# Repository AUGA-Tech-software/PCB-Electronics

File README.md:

# PCB-Electronics
 Projects of electronics projects on PCB

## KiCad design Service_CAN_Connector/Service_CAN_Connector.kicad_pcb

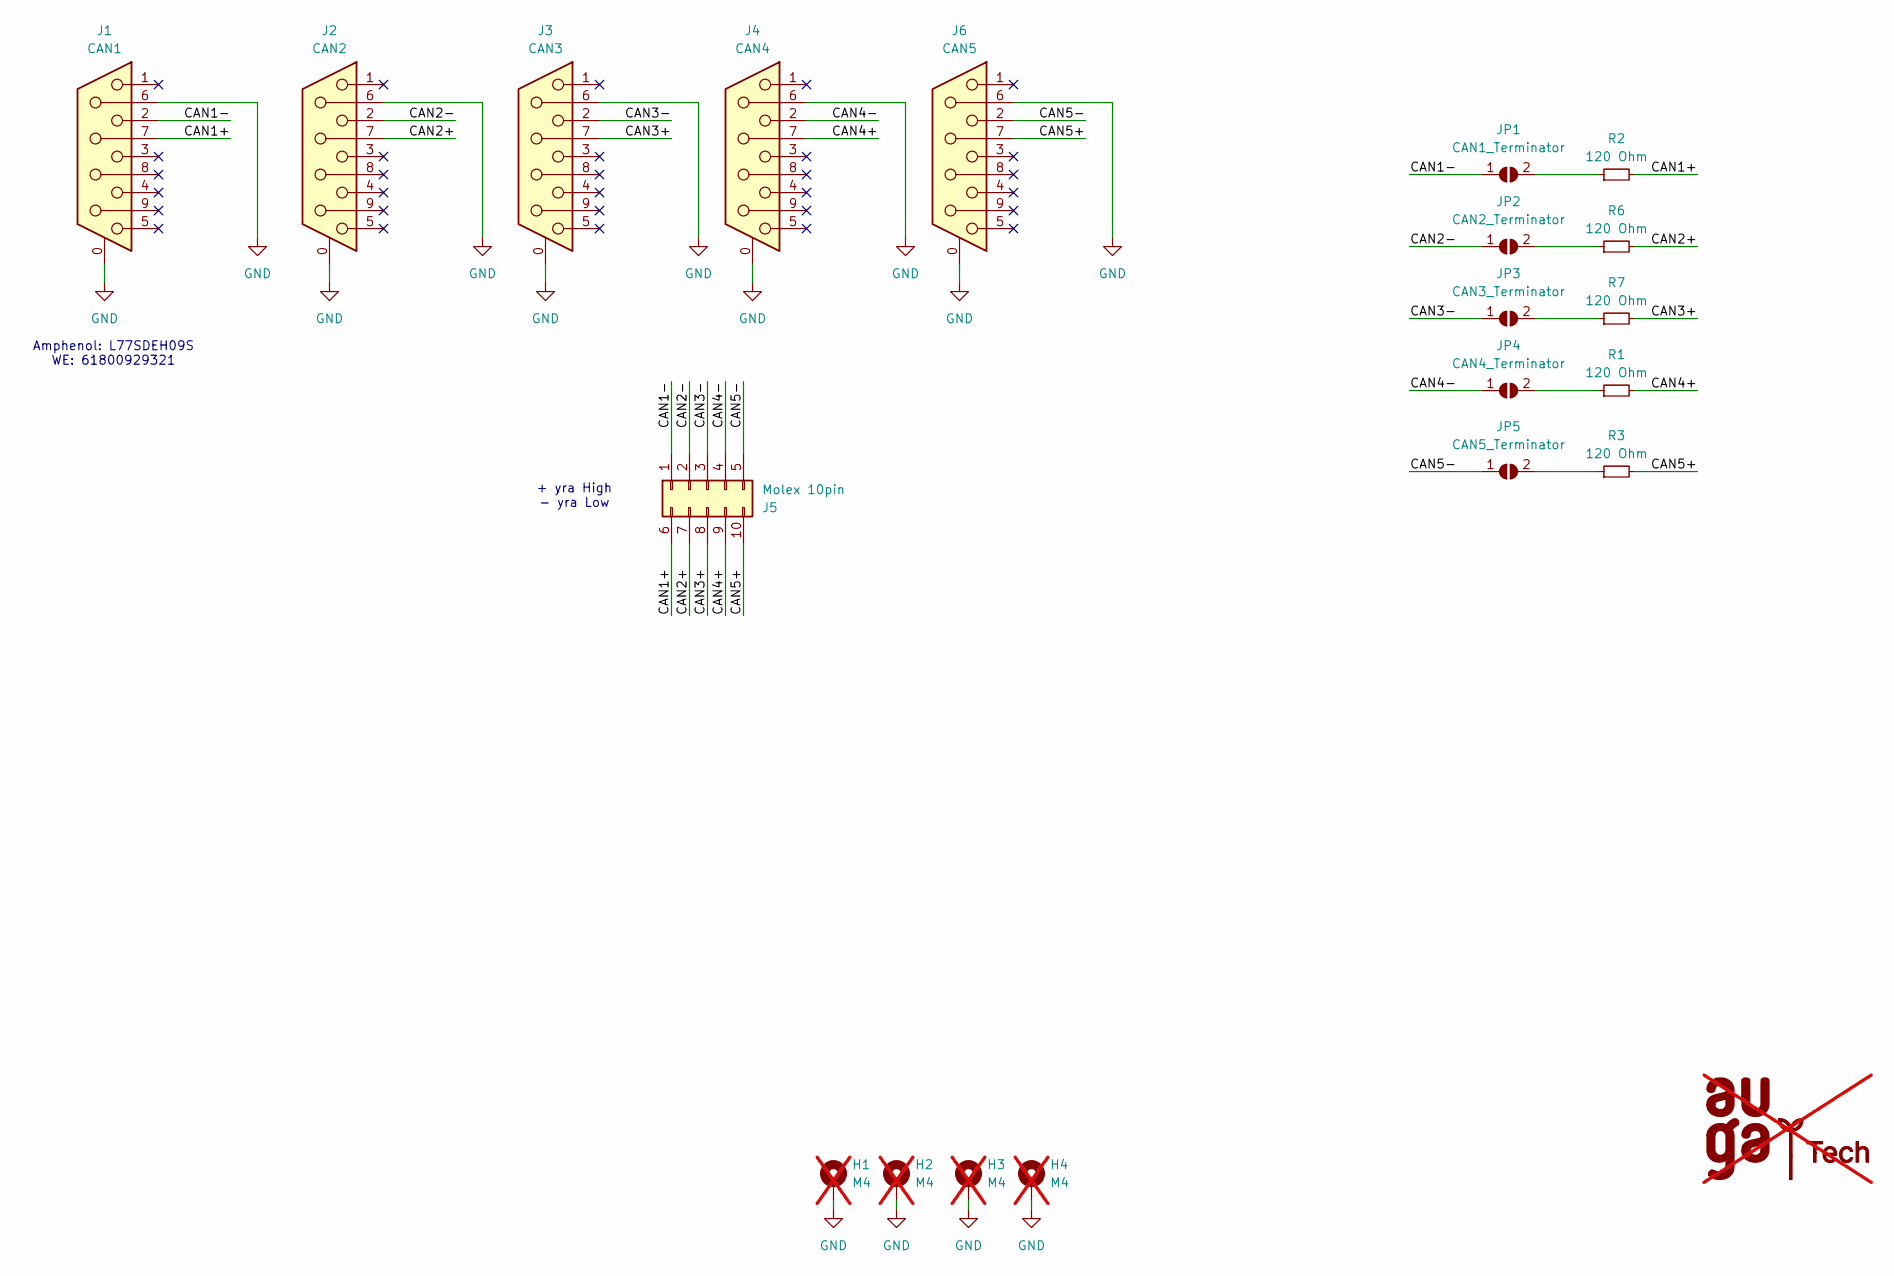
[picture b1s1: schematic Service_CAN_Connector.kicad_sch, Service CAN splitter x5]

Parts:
G1: AUGA-Tech-LOGO; AUGA-Tech-LOGO_12x15; not fitted
H1, H2, H3, H4: M4; MountingHole_4.3x6.2mm_M4_Pad_Via; not fitted
J1: CAN1; DSUB-9_Female_Vertical_P2.77x2.84mm_MountingHoles; JLCPCB Part # C19077342
J2: CAN2; DSUB-9_Female_Vertical_P2.77x2.84mm_MountingHoles; JLCPCB Part # C19077342
J3: CAN3; DSUB-9_Female_Vertical_P2.77x2.84mm_MountingHoles; JLCPCB Part # C19077342
J4: CAN4; DSUB-9_Female_Vertical_P2.77x2.84mm_MountingHoles; JLCPCB Part # C19077342
J5: Molex 10pin; Molex_Mini-Fit_Jr_5566-10A2_2x05_P4.20mm_Vertical; MFR_PN 39299103
J6: CAN5; DSUB-9_Female_Vertical_P2.77x2.84mm_MountingHoles; JLCPCB Part # C19077342
JP1: CAN1_Terminator; SolderJumper-2_P1.3mm_Open_RoundedPad1.0x1.5mm
JP2: CAN2_Terminator; SolderJumper-2_P1.3mm_Open_RoundedPad1.0x1.5mm
JP3: CAN3_Terminator; SolderJumper-2_P1.3mm_Open_RoundedPad1.0x1.5mm
JP4: CAN4_Terminator; SolderJumper-2_P1.3mm_Open_RoundedPad1.0x1.5mm
JP5: CAN5_Terminator; SolderJumper-2_P1.3mm_Open_RoundedPad1.0x1.5mm
R1, R2, R3, R6, R7: 120 Ohm; R_0805_2012Metric; JLCPCB Part # C17437

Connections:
/CAN1+: J1.7, J5.6, R2.2
/CAN1-: J1.2, J5.1, JP1.1 (A)
/CAN2+: J2.7, J5.7, R6.2
/CAN2-: J2.2, J5.2, JP2.1 (A)
/CAN3+: J3.7, J5.8, R7.2
/CAN3-: J3.2, J5.3, JP3.1 (A)
/CAN4+: J4.7, J5.9, R1.2
/CAN4-: J4.2, J5.4, JP4.1 (A)
/CAN5+: J5.10, J6.7, R3.2
/CAN5-: J5.5, J6.2, JP5.1 (A)
GND: H1.1, H2.1, H3.1, H4.1, J1.0 (PAD), J1.6, J2.0 (PAD), J2.6, J3.0 (PAD), J3.6, J4.0 (PAD), J4.6, J6.0 (PAD), J6.6
unnamed: JP1.2 (B), R2.1
unnamed: JP2.2 (B), R6.1
unnamed: JP3.2 (B), R7.1
unnamed: JP4.2 (B), R1.1
unnamed: JP5.2 (B), R3.1

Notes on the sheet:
Amphenol: L77SDEH09S WE: 61800929321
+ yra High - yra Low

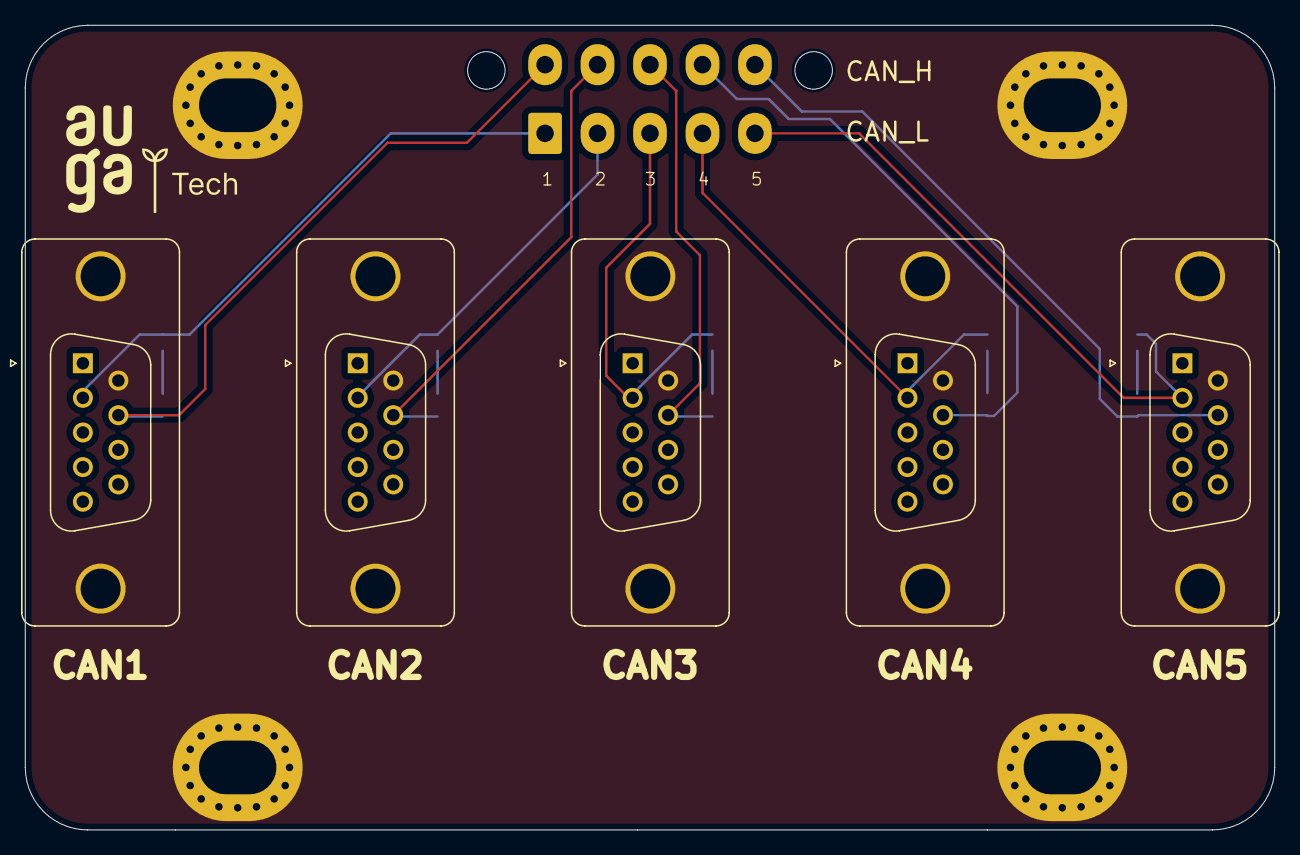
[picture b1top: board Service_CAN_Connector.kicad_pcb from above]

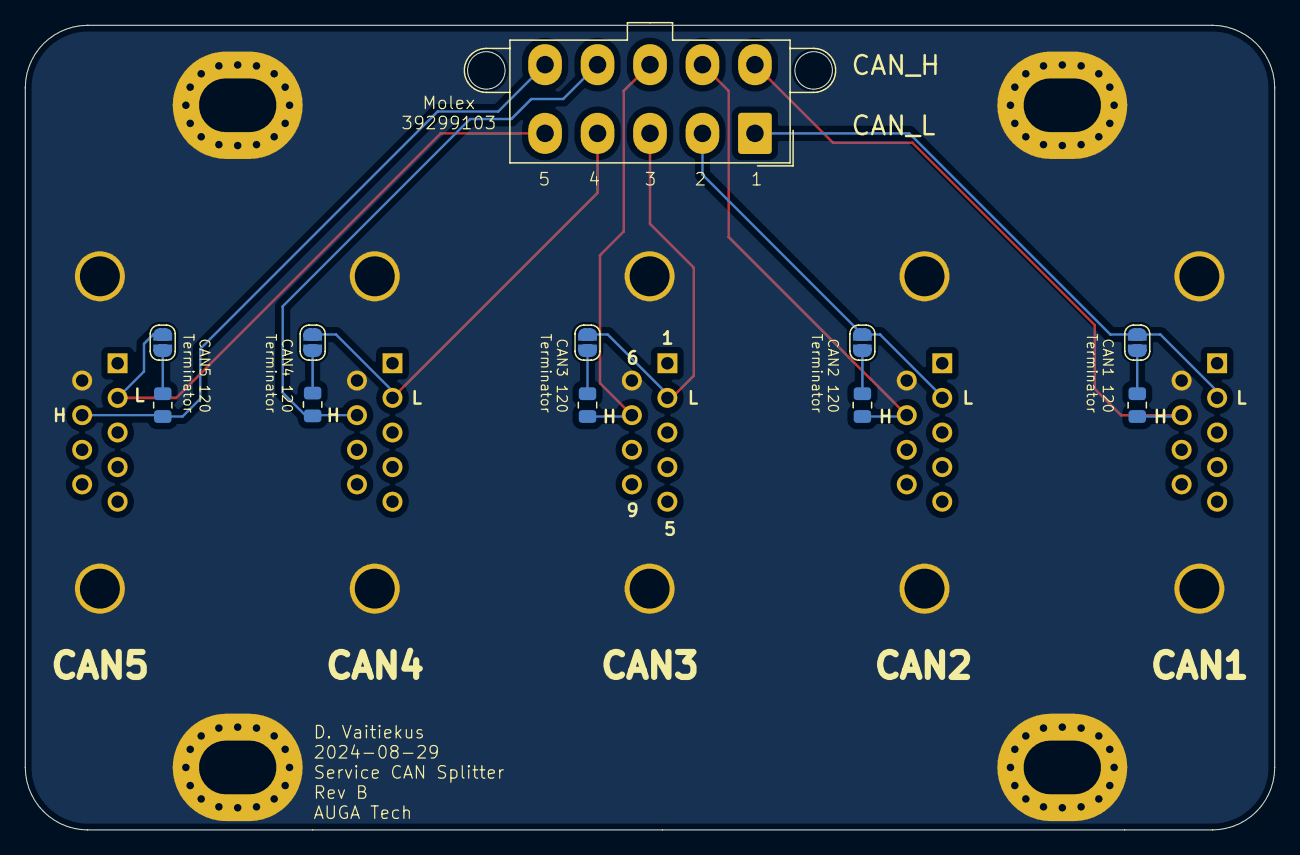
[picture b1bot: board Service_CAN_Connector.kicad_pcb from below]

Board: 2 copper layers, 100.0 x 64.4 mm, 21 parts (11 on the bottom side), 16 nets.

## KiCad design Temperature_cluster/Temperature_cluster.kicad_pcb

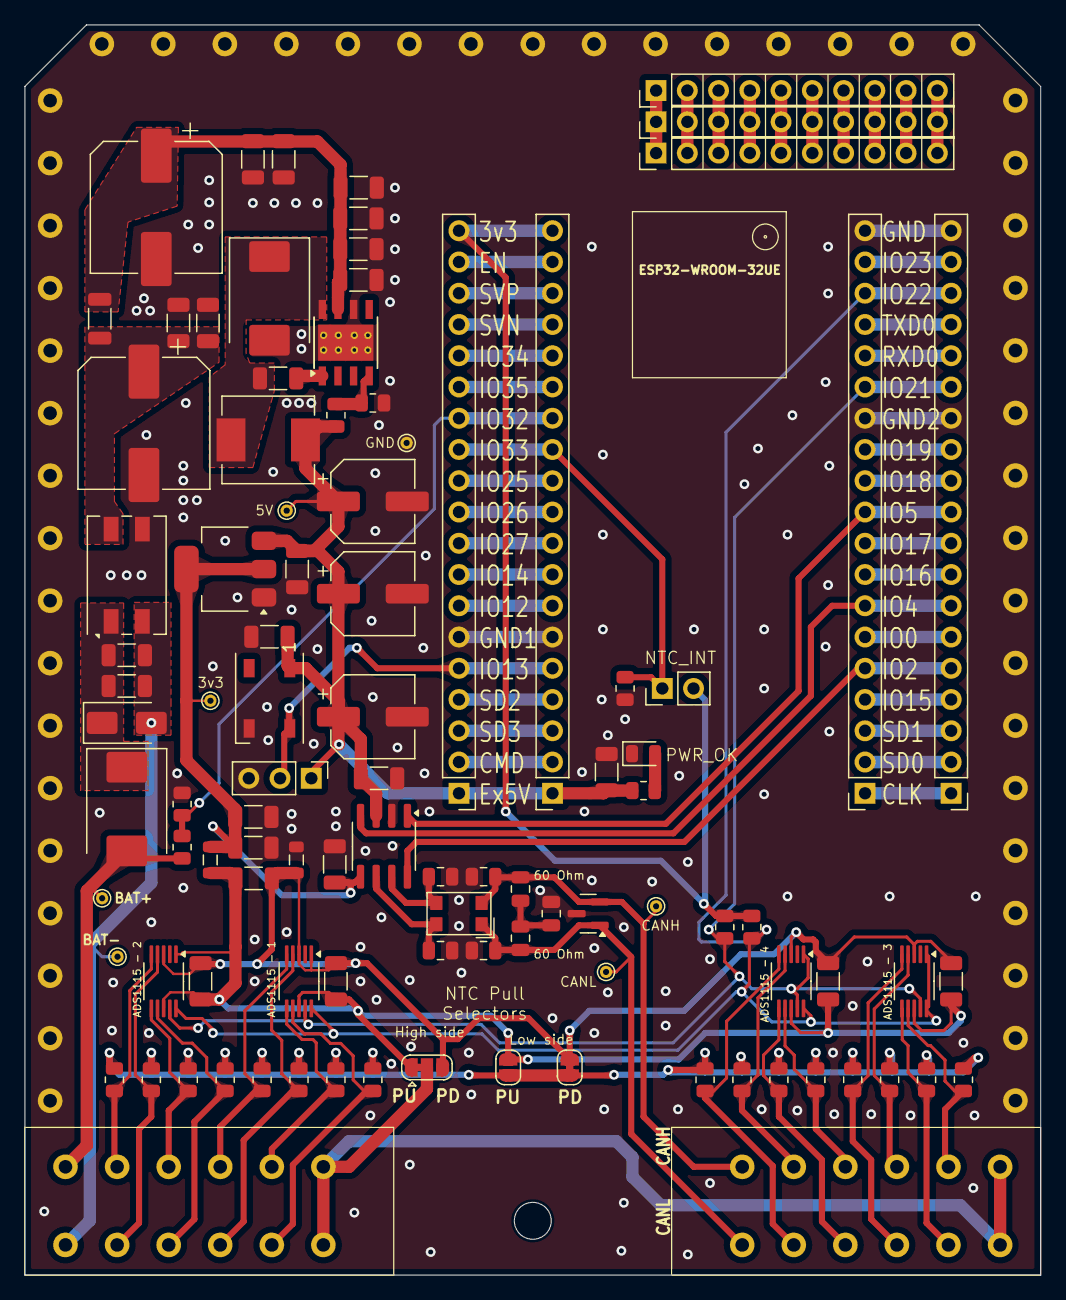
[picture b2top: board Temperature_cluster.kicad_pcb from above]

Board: 2 copper layers, 82.6 x 101.6 mm, 99 parts (1 on the bottom side), 81 nets.

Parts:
C1, C2, C7, C12, C16, C21, C22, C23, C25, C26, C28: 50V, 100nF; C_1206_3216Metric
C3, C4, C5, C6, C8, C9, C10, C11, C15, C20, C24: 50V, 10uF; C_1206_3216Metric
C13: 50V, 10nF; C_1206_3216Metric
C14, C19: 50v, 220uF; CP_Elec_10x10.5
C17, C18, C27: 10v, 220uF; CP_Elec_6.3x5.4
C29, C30, C31, C32: 100pF; C_0805_2012Metric
C33: 4n7 100V; C_0805_2012Metric
D1: WS2812B; LED_WS2812B_PLCC4_5.0x5.0mm_P3.2mm
D2, D4: B540C-13-F; D_SMC
D3: SMAJ26CA; D_SMA
D5: Power_OK; LED_0805_2012Metric
D6: NUP2105L; SOT-23
FB1, FB2: 500mA; L_0805_2012Metric
FL1: 500uH, 1kohm, 1A; Filter_Bourns_SRF0905_6.0x9.2mm
FL2: Filter_EMI; L_CommonModeChoke_1812
G1: AUGA-Tech-LOGO; AUGA-Tech-LOGO_23x15
J1: ESP32_Left; PinHeader_1x19_P2.54mm_Vertical
J2: DTM13-12PA-12PB; DTM13-12PA-12PB-R008
J3: ESP32_Right; PinHeader_1x19_P2.54mm_Vertical
J4: ESP32_Left; PinSocket_1x19_P2.54mm_Vertical
J5: ESP32_Right; PinSocket_1x19_P2.54mm_Vertical
J6: NTC_Internal; PinHeader_1x02_P2.54mm_Vertical
J7: EXTRA1; PinHeader_1x10_P2.54mm_Vertical
J8: EXTRA3; PinHeader_1x10_P2.54mm_Vertical
J9: EXTRA2; PinHeader_1x10_P2.54mm_Vertical
J10: Ext RGB connector; PinHeader_1x03_P2.54mm_Vertical
JP1: NTC-PullDown; SolderJumper-2_P1.3mm_Bridged_RoundedPad1.0x1.5mm
JP2: NTC-PullUp; SolderJumper-2_P1.3mm_Open_RoundedPad1.0x1.5mm
JP3: NTC_Input; SolderJumper-3_P1.3mm_Bridged12_RoundedPad1.0x1.5mm
L1: 15uH; L_Sunlord_MWSA0603S
L2: 2.2uH, 900mA; L_1206_3216Metric
R1, R2: 5.1k; R_0805_2012Metric
R7, R8, R9, R10, R11, R12, R13, R14, R15, R16, R17, R18, R19, R20, R21, R22, R24, R29, R30: 10K; R_0805_2012Metric
R23: 33k; R_0805_2012Metric
R25: 680; R_0805_2012Metric
R26, R27: 59R 1%; C_0805_2012Metric
R28: 100k; R_0805_2012Metric
TP1: VBat+; TestPoint_THTPad_D1.0mm_Drill0.5mm
TP2: VBat-; TestPoint_THTPad_D1.0mm_Drill0.5mm
TP3: 5V; TestPoint_THTPad_D1.0mm_Drill0.5mm
TP4: GND; TestPoint_THTPad_D1.0mm_Drill0.5mm
TP5: 3v3; TestPoint_THTPad_D1.0mm_Drill0.5mm
TP6: CANH; TestPoint_THTPad_D1.0mm_Drill0.5mm
TP7: CANL; TestPoint_THTPad_D1.0mm_Drill0.5mm
U2: ADS1115IDGS - 1; VSSOP-10_3x3mm_P0.5mm
U3: ADS1115IDGS - 3; VSSOP-10_3x3mm_P0.5mm
U4: ADS1115IDGS - 2; VSSOP-10_3x3mm_P0.5mm
U5: ADS1115IDGS - 4; VSSOP-10_3x3mm_P0.5mm
U6: TPS5430DDAR; TI_SO-PowerPAD-8_ThermalVias
U7: AMS1117-3.3; SOT-223-3_TabPin2
U8: TJA1051T-3; SOIC-8_3.9x4.9mm_P1.27mm

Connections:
+3.3VA: C3.2, C4.2, C5.2, C6.2, C25.1, FB1.2, JP2.2 (B), JP3.1 (A), U2.8 (VDD), U3.8 (VDD), U4.1 (ADDR), U4.8 (VDD), U5.8 (VDD)
+3.3VP: J3.19, J5.19, J6.2, R1.1, R2.1
+3V3: C23.2, C24.2, C26.1, FB1.1, TP5.1, U7.2 (VO), U8.5 (VIO)
+5V: C1.1, C2.1, C17.1, C18.1, C22.2, C27.1, C28.1, D1.1 (VDD), J3.1, J5.1, J10.1, L1.2, R23.2, R25.2, TP3.1, U7.3 (VI), U8.3 (VCC)
/CLK: J1.1, J4.1
/CMD: J3.2, J5.2
/EN: J3.18, J5.18
/IO0: J1.6, J4.6
/IO12: J3.7, J5.7
/IO14: J3.8, J5.8
/IO15: J1.4, J4.4
/IO16: J1.8, J4.8
/IO17: J1.9, J4.9
/IO18: J1.11, J4.11
/IO19: J1.12, J4.12
/IO23: J1.18, J4.18
/IO25: J3.11, J5.11
/IO26: J3.10, J5.10
/IO27: J3.9, J5.9
/IO34: J3.15, J5.15
/IO35: J3.14, J5.14
/NTC_1: J2.A8, R7.1, U4.5 (AIN1)
/NTC_2: J2.A9, R8.1, U4.6 (AIN2)
/NTC_3: J2.A10, R9.1, U2.5 (AIN1)
/NTC_4: J2.A11, R10.1, U2.6 (AIN2)
/NTC_5: J2.A2, R11.1, U2.7 (AIN3)
/NTC_6: J2.A3, R12.1, U2.4 (AIN0)
/NTC_7: J2.A4, R13.1, U4.7 (AIN3)
/NTC_8: J2.A5, R14.1, U4.4 (AIN0)
/NTC_9: J2.B2, R15.1, U5.4 (AIN0)
/NTC_10: J2.B3, R16.1, U5.7 (AIN3)
/NTC_11: J2.B4, R17.1, U3.4 (AIN0)
/NTC_12: J2.B5, R18.1, U3.7 (AIN3)
/NTC_13: J2.B8, R19.1, U3.6 (AIN2)
/NTC_14: J2.B9, R20.1, U3.5 (AIN1)
/NTC_15: J2.B10, R21.1, U5.6 (AIN2)
/NTC_16: J2.B11, R22.1, U5.5 (AIN1)
/NTC_INT: J3.12, J5.12, J6.1, R29.1
/NTC_Input: J2.A1, J2.A12, J2.B6, J2.B7, JP3.2 (C)
/Power_module/BOOT: C13.1, U6.1 (BOOT)
/Power_module/PH: C13.2, D4.1 (K), L1.1, U6.8 (PH)
/Power_module/VSENSE: R23.1, R24.2, U6.4 (VSENSE)
/RXD0: J1.15, J4.15
/SD0: J1.2, J4.2
/SD1: J1.3, J4.3
/SD2: J3.4, J5.4
/SD3: J3.3, J5.3
/TXD0: J1.16, J4.16
/VBAT_Sense: J3.13, J5.13, R28.2, R30.2
/VN: J3.16, J5.16
/VP: J3.17, J5.17
/WS_LED: D1.4 (DIN), J3.5, J5.5, J10.2
/i2c_ADDR-3: J1.17, J4.17, R2.2, U2.10 (SCL), U3.1 (ADDR), U3.10 (SCL), U4.10 (SCL), U5.10 (SCL)
/i2c_ADDR-4: J1.14, J4.14, R1.2, U2.9 (SDA), U3.9 (SDA), U4.9 (SDA), U5.1 (ADDR), U5.9 (SDA)
CAN_H: C31.2, D6.2 (K), FL2.2, J2.B1, R26.1, TP6.1
CAN_L: C32.1, D6.1 (K), FL2.1, J2.B12, R27.2, TP7.1
CAN_RX: J1.7, J4.7, U8.4 (RXD)
CAN_S: J1.5, J4.5, U8.8 (S)
CAN_TX: J1.10, J4.10, U8.1 (TXD)
GND: C1.2, C2.2, C7.2, C8.1, C9.1, C10.1, C14.2, C15.1, C16.2, C17.2, C18.2, C19.2, C20.1, C21.2, C22.1, C23.1, C24.1, C26.2, C27.2, C28.2, C29.2, C30.1, C31.1, C32.2, C33.2, D1.3 (VSS), D4.2 (A), D5.1 (K), D6.3 (A), FB2.1, FL1.3, J1.13, J1.19, J2.13 (GND), J3.6, J4.13, J4.19, J5.6, J10.3, R24.1, R29.2, R30.1, TP4.1, U6.6 (GND), U6.9 (GNDPAD), U7.1 (GND), U8.2 (GND)
GNDA: C3.1, C4.1, C5.1, C6.1, C25.2, FB2.2, JP1.2 (B), JP3.3 (B), U2.1 (ADDR), U2.3 (GND), U3.3 (GND), U4.3 (GND), U5.3 (GND)
unnamed: C14.1, C15.2, C16.1, FL1.4, L2.1
unnamed: C33.1, R26.2, R27.1
unnamed: C11.2, C12.1, D2.1 (K), D3.1 (A1), FL1.1
unnamed: D5.2 (A), R25.1
unnamed: J7.1, J8.1, J9.1
unnamed: J7.2, J8.2, J9.2
unnamed: J7.3, J8.3, J9.3
unnamed: J7.4, J8.4, J9.4
unnamed: J7.5, J8.5, J9.5
unnamed: J7.6, J8.6, J9.6
unnamed: J7.7, J8.7, J9.7
unnamed: J7.8, J8.8, J9.8
unnamed: J7.9, J8.9, J9.9
unnamed: J7.10, J8.10, J9.10
unnamed: JP1.1 (A), JP2.1 (A), R7.2, R8.2, R9.2, R10.2, R11.2, R12.2, R13.2, R14.2, R15.2, R16.2, R17.2, R18.2, R19.2, R20.2, R21.2, R22.2
unnamed: C30.2, FL2.3, U8.7 (CANH)
unnamed: C29.1, FL2.4, U8.6 (CANL)
VBat+: D2.2 (A), J2.A7, R28.1, TP1.1
VBat-: C11.1, C12.2, D3.2 (A2), FL1.2, J2.A6, TP2.1
Vin_Filtered: C7.1, C8.2, C9.2, C10.2, C19.1, C20.2, C21.1, L2.2, U6.7 (VIN)

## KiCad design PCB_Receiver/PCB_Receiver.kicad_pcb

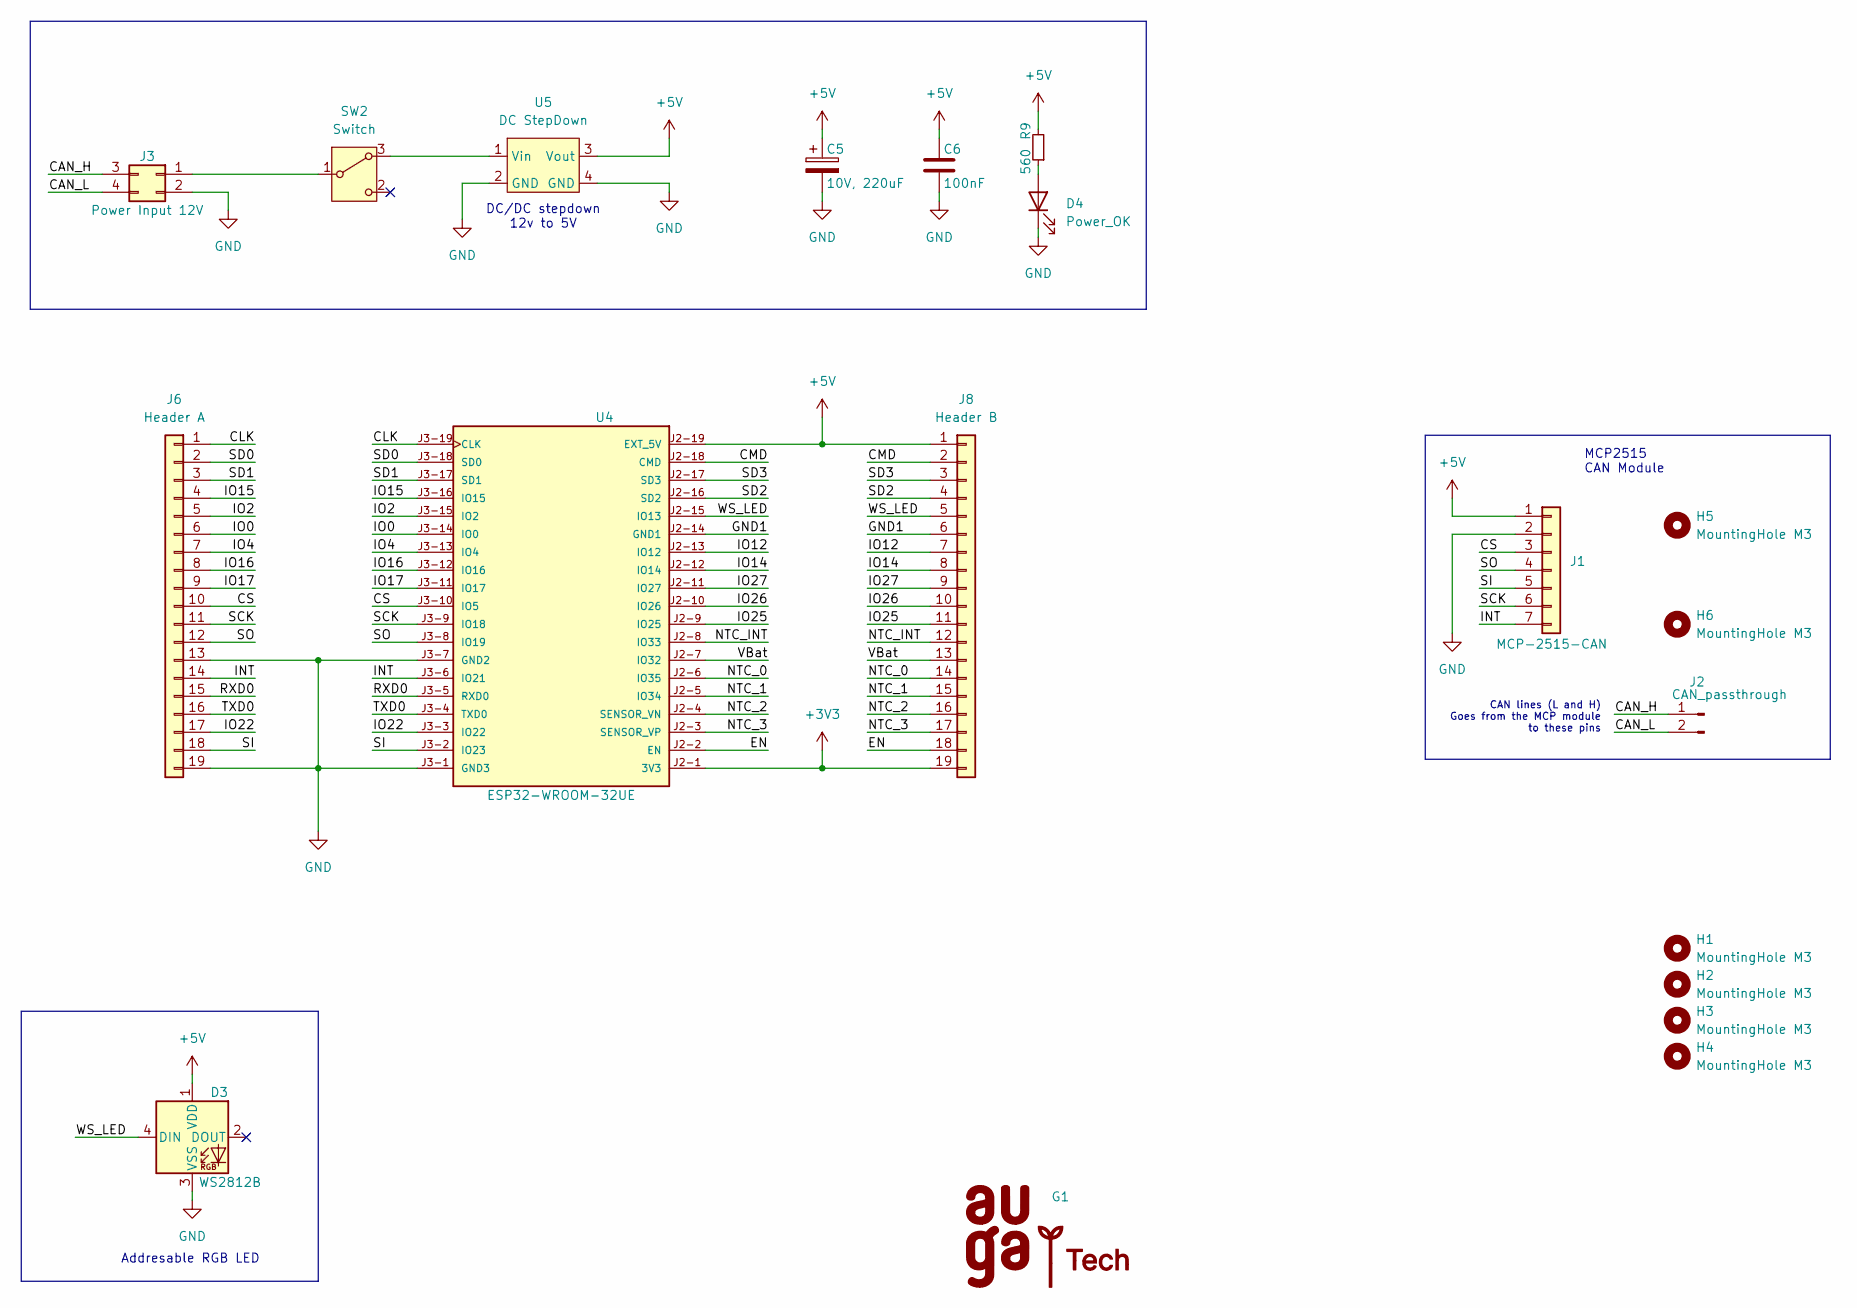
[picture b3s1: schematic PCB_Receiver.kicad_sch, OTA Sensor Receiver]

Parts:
C5: 10V, 220uF; CP_Radial_D6.3mm_P2.50mm; Part No 860020273009
C6: 100nF; C_Disc_D3.8mm_W2.6mm_P2.50mm
D3: WS2812B; LED_WS2812B_PLCC4_5.0x5.0mm_P3.2mm
D4: Power_OK; LED_D5.0mm
G1: AUGA-Tech-LOGO; AUGA-Tech-footprint
H1, H2, H3, H4, H5, H6: MountingHole M3; MountingHole_3.2mm_M3
J1: MCP-2515-CAN; PinHeader_1x07_P2.54mm_Vertical
J2: CAN_passthrough; PinHeader_1x02_P2.54mm_Vertical
J3: Power Input 12V; Molex_Mini-Fit_Jr_5569-04A2_2x02_P4.20mm_Horizontal
J6: Header A; PinHeader_1x19_P2.54mm_Vertical
J8: Header B; PinHeader_1x19_P2.54mm_Vertical
R9: 560; R_Axial_DIN0207_L6.3mm_D2.5mm_P10.16mm_Horizontal
SW2: Switch; SW_Slide-03_Wuerth-WS-SLTV_10x2.5x6.4_P2.54mm
U4: ESP32-WROOM-32UE; MODULE_ESP32-DEVKITC-32D
U5: DC StepDown; DCDC_StepDown

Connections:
+3V3: J8.19, U4.J2-1 (3V3)
+5V: C5.1, C6.1, D3.1 (VDD), J1.1, J8.1, R9.2, U4.J2-19 (EXT_5V), U5.3 (Vout)
/CAN_H: J2.1, J3.3
/CAN_L: J2.2, J3.4
/CLK: J6.1, U4.J3-19 (CLK)
/CMD: J8.2, U4.J2-18 (CMD)
/CS: J1.3, J6.10, U4.J3-10 (IO5)
/EN: J8.18, U4.J2-2 (EN)
/GND1: J8.6, U4.J2-14 (GND1)
/INT: J1.7, J6.14, U4.J3-6 (IO21)
/IO0: J6.6, U4.J3-14 (IO0)
/IO2: J6.5, U4.J3-15 (IO2)
/IO4: J6.7, U4.J3-13 (IO4)
/IO12: J8.7, U4.J2-13 (IO12)
/IO14: J8.8, U4.J2-12 (IO14)
/IO15: J6.4, U4.J3-16 (IO15)
/IO16: J6.8, U4.J3-12 (IO16)
/IO17: J6.9, U4.J3-11 (IO17)
/IO22: J6.17, U4.J3-3 (IO22)
/IO25: J8.11, U4.J2-9 (IO25)
/IO26: J8.10, U4.J2-10 (IO26)
/IO27: J8.9, U4.J2-11 (IO27)
/NTC_0: J8.14, U4.J2-6 (IO35)
/NTC_1: J8.15, U4.J2-5 (IO34)
/NTC_2: J8.16, U4.J2-4 (SENSOR_VN)
/NTC_3: J8.17, U4.J2-3 (SENSOR_VP)
/NTC_INT: J8.12, U4.J2-8 (IO33)
/RXD0: J6.15, U4.J3-5 (RXD0)
/SCK: J1.6, J6.11, U4.J3-9 (IO18)
/SD0: J6.2, U4.J3-18 (SD0)
/SD1: J6.3, U4.J3-17 (SD1)
/SD2: J8.4, U4.J2-16 (SD2)
/SD3: J8.3, U4.J2-17 (SD3)
/SI: J1.5, J6.18, U4.J3-2 (IO23)
/SO: J1.4, J6.12, U4.J3-8 (IO19)
/TXD0: J6.16, U4.J3-4 (TXD0)
/VBat: J8.13, U4.J2-7 (IO32)
/WS_LED: D3.4 (DIN), J8.5, U4.J2-15 (IO13)
GND: C5.2, C6.2, D3.3 (VSS), D4.1 (K), J1.2, J3.2, J6.13, J6.19, U4.J3-1 (GND3), U4.J3-7 (GND2), U5.2 (GND), U5.4 (GND)
unnamed: D4.2 (A), R9.1
unnamed: J3.1, SW2.1 (B)
unnamed: SW2.3 (A), U5.1 (Vin)

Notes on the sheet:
DC/DC stepdown 12v to 5V
CAN lines (L and H) Goes from the MCP module to these pins
MCP2515 CAN Module
Addresable RGB LED

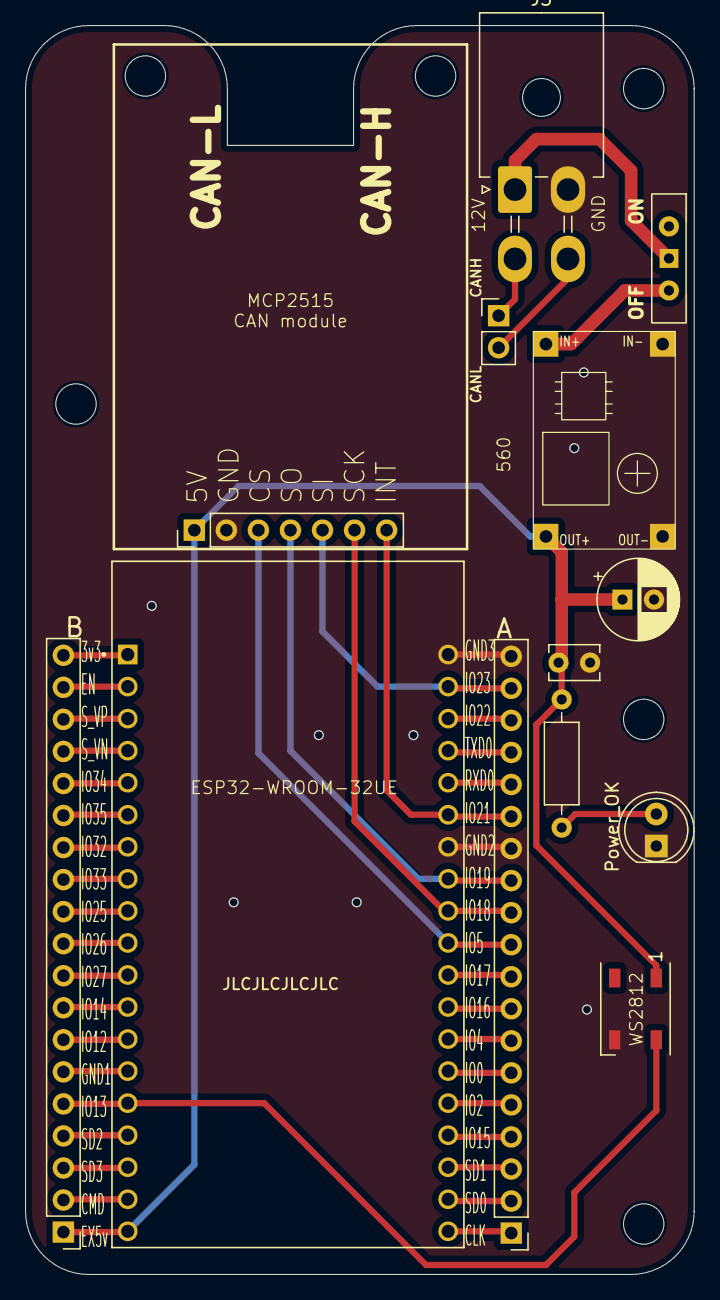
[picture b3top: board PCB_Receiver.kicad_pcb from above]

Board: 2 copper layers, 53.0 x 99.0 mm, 20 parts (1 on the bottom side), 42 nets.

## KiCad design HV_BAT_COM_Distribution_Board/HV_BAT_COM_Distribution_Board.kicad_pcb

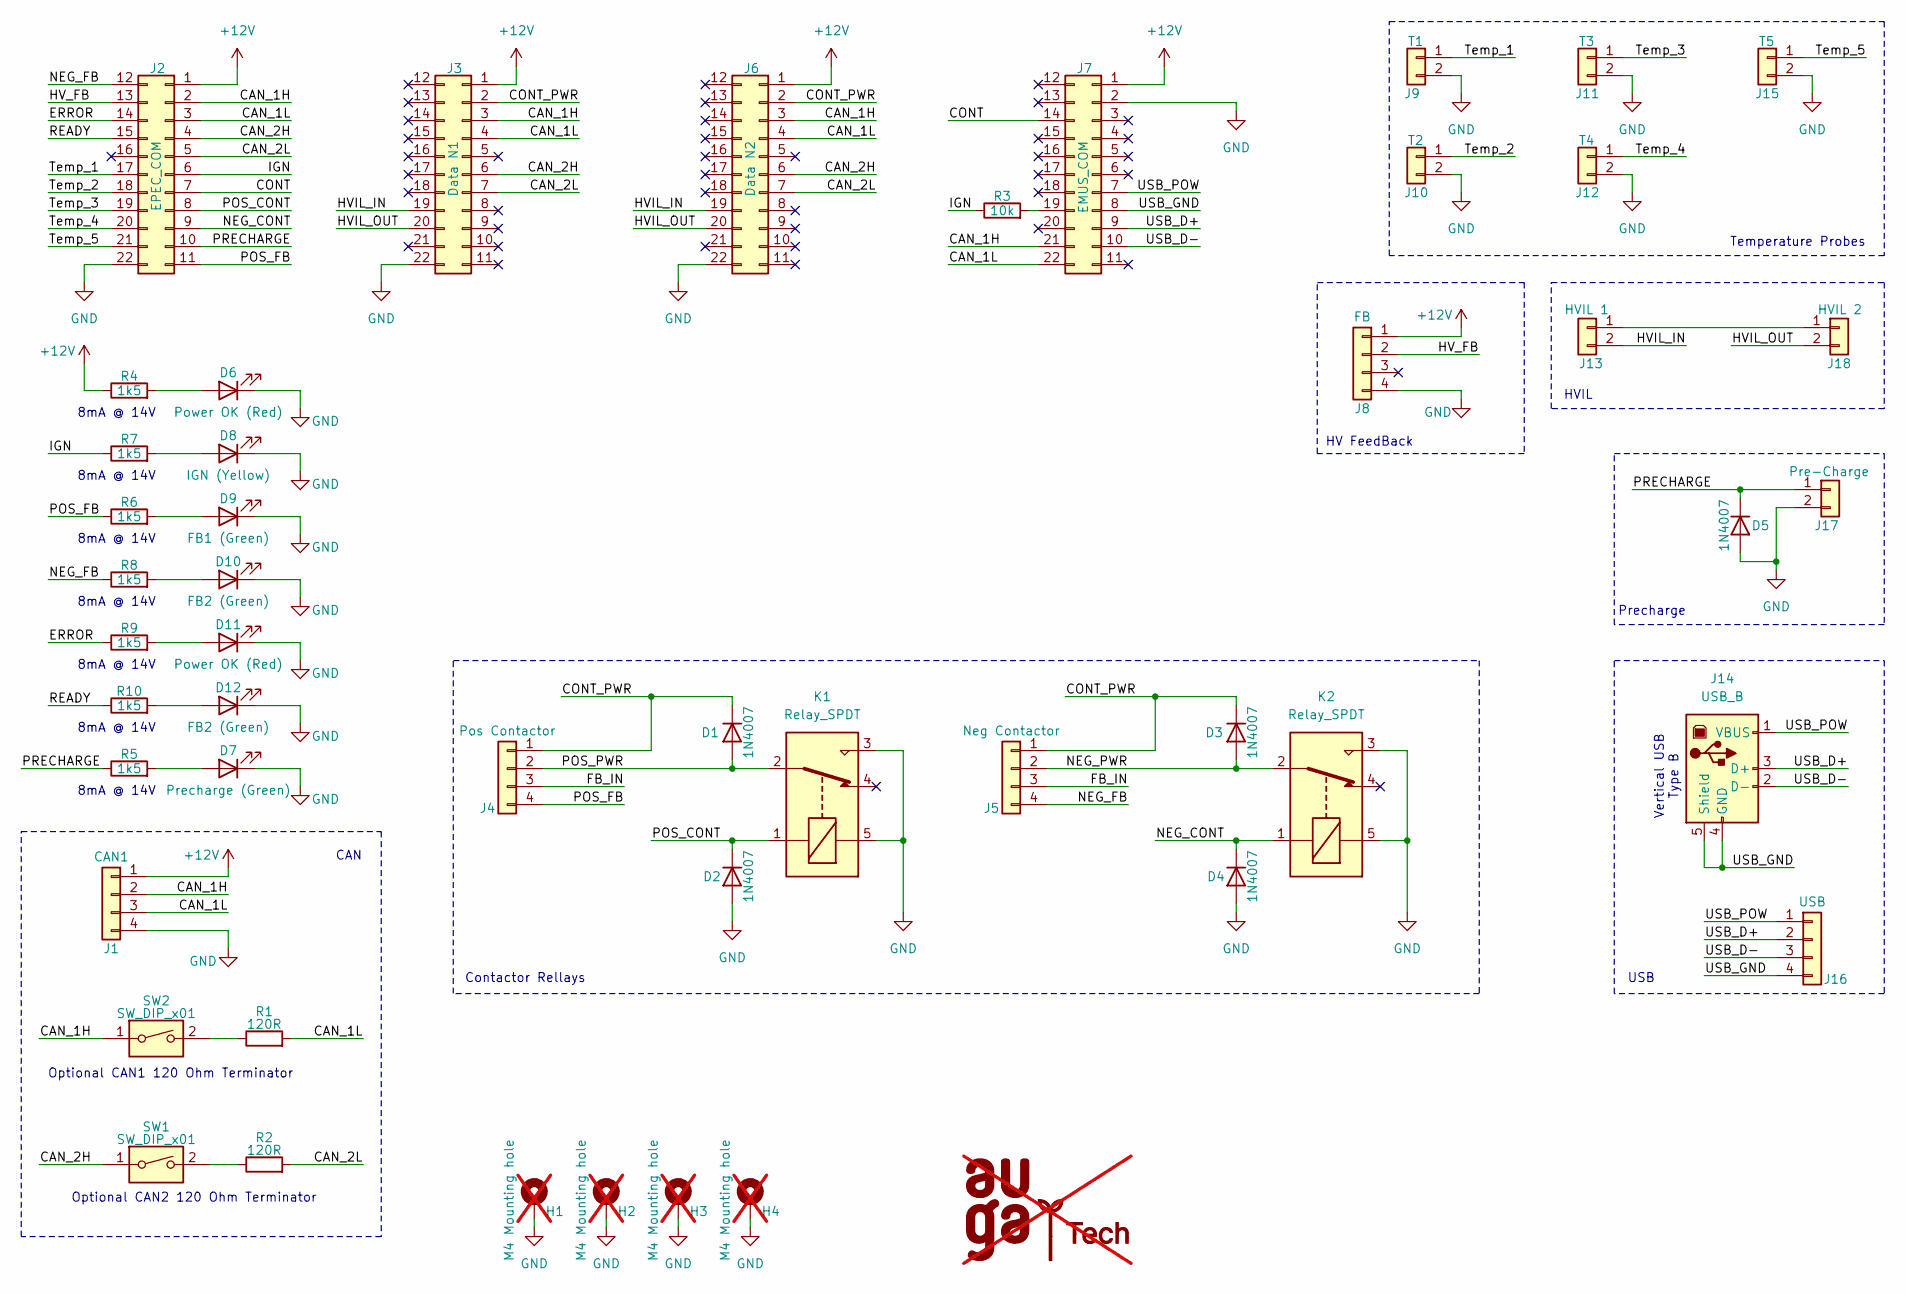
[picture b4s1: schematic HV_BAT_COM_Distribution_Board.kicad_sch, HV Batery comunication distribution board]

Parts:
D1, D2, D3, D4, D5: 1N4007; D_SMA; JLCPCB Part # C2909831
D6, D11: Power OK (Red); LED_0805_2012Metric; JLCPCB Part # C84256
D7: Precharge (Green); LED_0805_2012Metric; JLCPCB Part # C2297
D8: IGN (Yellow); LED_0805_2012Metric; JLCPCB Part # C2296
D9: FB1 (Green); LED_0805_2012Metric; JLCPCB Part # C2297
D10, D12: FB2 (Green); LED_0805_2012Metric; JLCPCB Part # C2297
G1: AUGA-Tech-LOGO; AUGA-Tech-LOGO_12x15; not fitted
H1, H2, H3, H4: M4 Mounting hole; MountingHole_4.3x6.2mm_M4_Pad; not fitted
J1: CAN1; Molex_Micro-Fit_3.0_43045-0412_2x02_P3.00mm_Vertical; MPN 430450412; JLCPCB Part # C277721
J2: EPEC_COM; Molex_Micro-Fit_3.0_43045-2212_2x11_P3.00mm_Vertical; MPN 430452224; JLCPCB Part # C492366
J3: Data N1; Molex_Micro-Fit_3.0_43045-2212_2x11_P3.00mm_Vertical; MPN 430452224; JLCPCB Part # C492366
J4: Pos Contactor; Molex_Micro-Fit_3.0_43045-0412_2x02_P3.00mm_Vertical; MPN 430450412; JLCPCB Part # C277721
J5: Neg Contactor; Molex_Micro-Fit_3.0_43045-0412_2x02_P3.00mm_Vertical; MPN 430450412; JLCPCB Part # C277721
J6: Data N2; Molex_Micro-Fit_3.0_43045-2212_2x11_P3.00mm_Vertical; MPN 430452224; JLCPCB Part # C492366
J7: EMUS_COM; Molex_Micro-Fit_3.0_43045-2212_2x11_P3.00mm_Vertical; MPN 430452224; JLCPCB Part # C492366
J8: FB; Molex_Micro-Fit_3.0_43045-0412_2x02_P3.00mm_Vertical; MPN 430450412; JLCPCB Part # C277721
J9: T1; Molex_Micro-Fit_3.0_43045-0212_2x01_P3.00mm_Vertical; MPN 430450212; JLCPCB Part # C293362
J10: T2; Molex_Micro-Fit_3.0_43045-0212_2x01_P3.00mm_Vertical; MPN 430450212; JLCPCB Part # C293362
J11: T3; Molex_Micro-Fit_3.0_43045-0212_2x01_P3.00mm_Vertical; MPN 430450212; JLCPCB Part # C293362
J12: T4; Molex_Micro-Fit_3.0_43045-0212_2x01_P3.00mm_Vertical; MPN 430450212; JLCPCB Part # C293362
J13: HVIL 1; Molex_Micro-Fit_3.0_43045-0212_2x01_P3.00mm_Vertical; MPN 430450212; JLCPCB Part # C293362
J14: USB_B; USB_B_TE_5787834_Vertical; MPN 61400413321; JLCPCB Part # C592900
J15: T5; Molex_Micro-Fit_3.0_43045-0212_2x01_P3.00mm_Vertical; MPN 430450212; JLCPCB Part # C293362
J16: USB; Molex_Micro-Fit_3.0_43045-0412_2x02_P3.00mm_Vertical; MPN 430450412; JLCPCB Part # C277721
J17: Pre-Charge; Molex_Micro-Fit_3.0_43045-0212_2x01_P3.00mm_Vertical; MPN 430450212; JLCPCB Part # C293362
J18: HVIL 2; Molex_Micro-Fit_3.0_43045-0212_2x01_P3.00mm_Vertical; MPN 430450212; JLCPCB Part # C293362
K1, K2: Relay_SPDT; Relay_SPDT_Omron-G5Q-1; MPN G5Q-1EU DC12; JLCPCB Part # C225715
R1, R2: 120R; R_0805_2012Metric; JLCPCB Part # C17437
R3: 10k; R_0805_2012Metric; JLCPCB Part # C17414
R4, R5, R6, R7, R8, R9, R10: 1k5; R_0805_2012Metric; JLCPCB Part # C4310
SW1, SW2: SW_DIP_x01; SW_DIP_SPSTx01_Slide_9.78x4.72mm_W7.62mm_P2.54mm; JLCPCB Part # C126888

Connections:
+12V: J1.1, J2.1, J3.1, J6.1, J7.1, J8.1, R4.1
/CAN_1H: J1.2, J2.2, J3.3, J6.3, J7.21, SW2.1
/CAN_1L: J1.3, J2.3, J3.4, J6.4, J7.22, R1.2
/CAN_2H: J2.4, J3.6, J6.6, SW1.1
/CAN_2L: J2.5, J3.7, J6.7, R2.2
/CONT: J2.7, J7.14
/CONT_PWR: D1.1 (K), D3.1 (K), J3.2, J4.1, J5.1, J6.2
/ERROR: J2.14, R9.1
/FB_IN: J4.3, J5.3
/HVIL_IN: J3.19, J6.19, J13.2
/HVIL_OUT: J3.20, J6.20, J18.2
/HV_FB: J2.13, J8.2
/IGN: J2.6, R3.1, R7.1
/NEG_CONT: D4.1 (K), J2.9, K2.1
/NEG_FB: J2.12, J5.4, R8.1
/NEG_PWR: D3.2 (A), J5.2, K2.2
/POS_CONT: D2.1 (K), J2.8, K1.1
/POS_FB: J2.11, J4.4, R6.1
/POS_PWR: D1.2 (A), J4.2, K1.2
/PRECHARGE: D5.1 (K), J2.10, J17.1, R5.1
/READY: J2.15, R10.1
/Temp_1: J2.17, J9.1
/Temp_2: J2.18, J10.1
/Temp_3: J2.19, J11.1
/Temp_4: J2.20, J12.1
/Temp_5: J2.21, J15.1
/USB_D+: J7.9, J14.3 (D+), J16.2
/USB_D-: J7.10, J14.2 (D-), J16.3
/USB_GND: J7.8, J14.4 (GND), J14.5 (Shield), J16.4
/USB_POW: J7.7, J14.1 (VBUS), J16.1
GND: D2.2 (A), D4.2 (A), D5.2 (A), D6.1 (K), D7.1 (K), D8.1 (K), D9.1 (K), D10.1 (K), D11.1 (K), D12.1 (K), H1.1, H2.1, H3.1, H4.1, J1.4, J2.22, J3.22, J6.22, J7.2, J8.4, J9.2, J10.2, J11.2, J12.2, J15.2, J17.2, K1.3, K1.5, K2.3, K2.5
unnamed: D6.2 (A), R4.2
unnamed: D7.2 (A), R5.2
unnamed: D8.2 (A), R7.2
unnamed: D9.2 (A), R6.2
unnamed: D10.2 (A), R8.2
unnamed: D11.2 (A), R9.2
unnamed: D12.2 (A), R10.2
unnamed: J7.19, R3.2
unnamed: J13.1, J18.1
unnamed: R1.1, SW2.2
unnamed: R2.1, SW1.2

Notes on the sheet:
8mA @ 14V
CAN
Optional CAN2 120 Ohm Terminator
HV FeedBack
USB
Temperature Probes
Vertical USB Type B
Precharge
Optional CAN1 120 Ohm Terminator
HVIL
Contactor Rellays

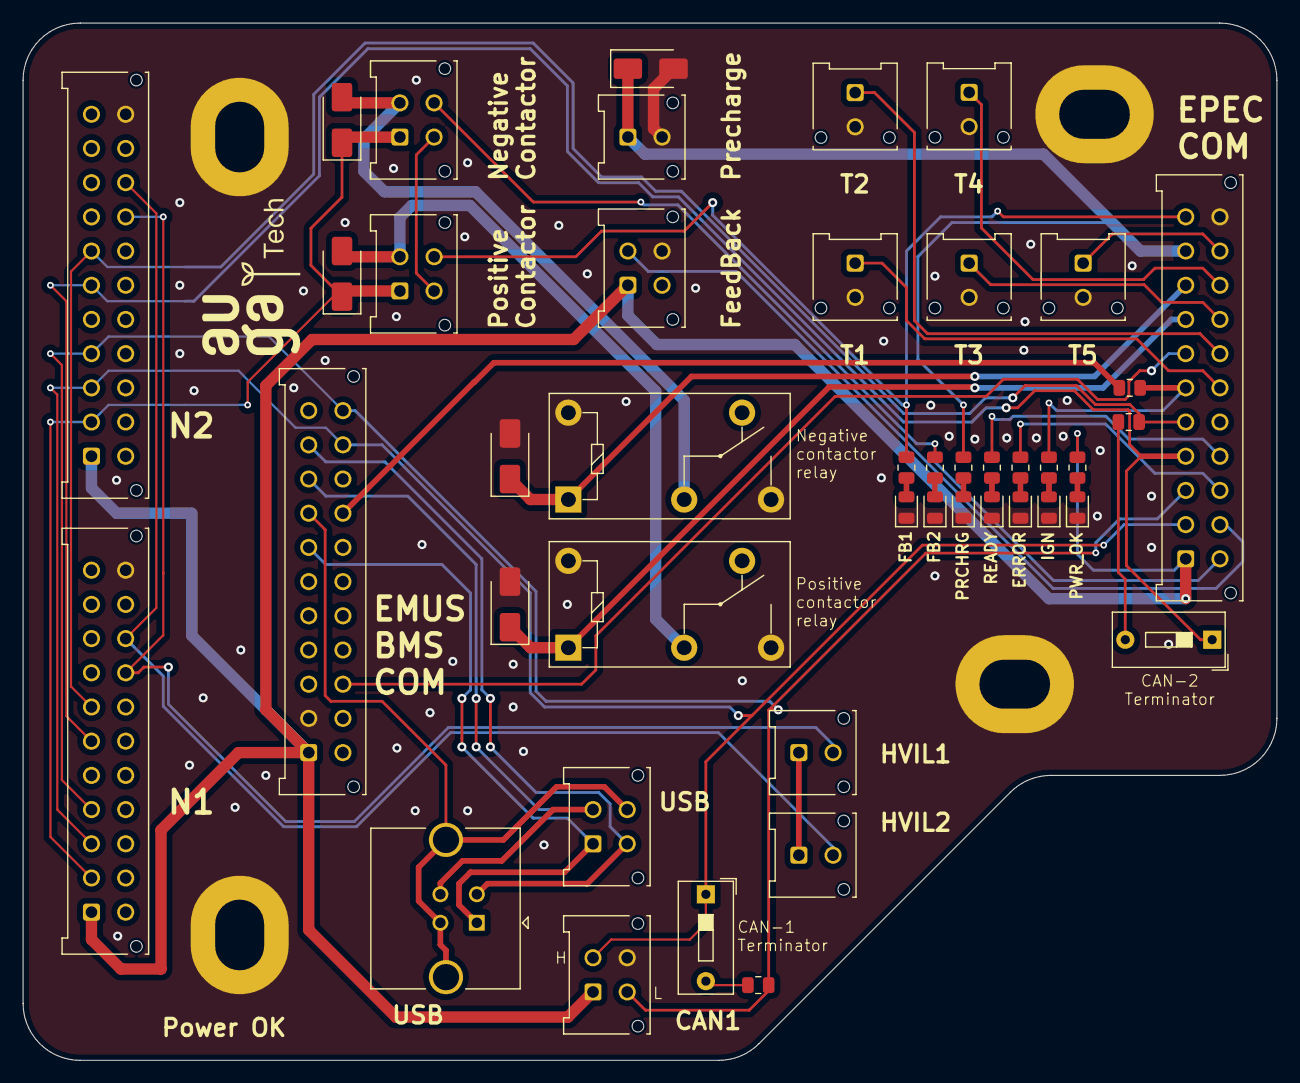
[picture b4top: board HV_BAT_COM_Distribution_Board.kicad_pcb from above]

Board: 2 copper layers, 110.0 x 91.0 mm, 50 parts (1 on the bottom side), 42 nets.

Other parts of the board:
G1#2: AUGA-Tech-LOGO; AUGA-Tech-LOGO_12x15
